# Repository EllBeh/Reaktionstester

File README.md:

# Reaktionstester
Aufbau und Entwurf eines einfachen Reaktionstesters auf dem ATMEGA328P in C. Das Repository enthält dabei den Code sowie den Schaltplan und das Platinen-Layout. Der Code wurde auf dem Arduino UNO ausgeführt werden, weshalb die Code-Struktur der Arduinostruktur entspricht.

## Programmablaufplan

___
## Schaltplan

___
## Platinenlayout

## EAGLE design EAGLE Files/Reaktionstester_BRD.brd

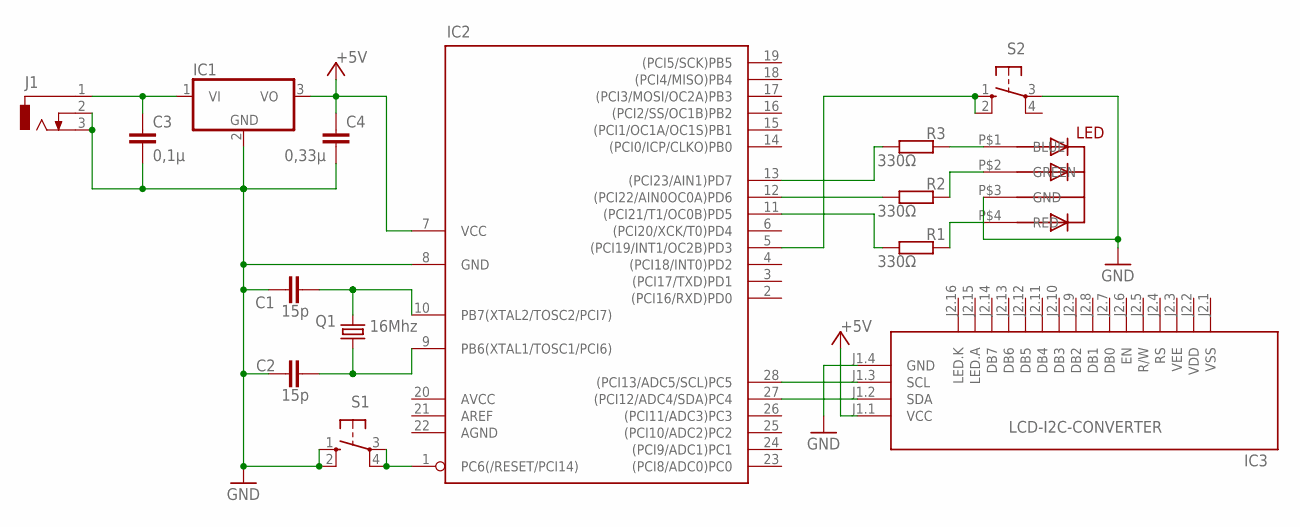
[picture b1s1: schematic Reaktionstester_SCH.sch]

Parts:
C1, C2: 15p; C5B3.5
C3: 0,1µ; C025-024X044
C4: 0,33µ; C025-024X044
IC1: 7805T; TO220H
IC2: ATMEGA328-20P; DIL28-3
IC3: LCD-I2C-CONVERTER
J1: DCJ0202
LED: 5MMRGBLED; LED5MMRGB
Q1: 16Mhz; 11.4X4.5
R1, R2, R3: 330Ω; 0204/5
S1, S2: 10-XX; B3F-10XX

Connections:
+5V: C4.1, IC1.3 (VO), IC2.7 (VCC), IC3.J1.1 (VCC)
GND: C1.1, C2.1, C3.2, C4.2, IC1.2 (GND), IC2.8 (GND), IC3.J1.4 (GND), J1.2, J1.3, LED.P$3 (GND), S1.1 (S), S1.2 (S1), S2.3, S2.4 (P1)
unnamed: C1.2, IC2.10 (PB7(XTAL2/TOSC2/PCI7)), Q1.2
unnamed: LED.P$1 (BLUE), R3.1
unnamed: C2.2, IC2.9 (PB6(XTAL1/TOSC1/PCI6)), Q1.1
unnamed: IC2.11 ((PCI21/T1/OC0B)PD5), R1.2
unnamed: IC2.5 ((PCI19/INT1/OC2B)PD3), S2.1 (S), S2.2 (S1)
unnamed: IC2.12 ((PCI22/AIN0OC0A)PD6), R2.2
unnamed: IC2.13 ((PCI23/AIN1)PD7), R3.2
unnamed: C3.1, IC1.1 (VI), J1.1
unnamed: LED.P$2 (GREEN), R2.1
unnamed: LED.P$4 (RED), R1.1
unnamed: IC2.28 ((PCI13/ADC5/SCL)PC5), IC3.J1.3 (SCL)
unnamed: IC2.1 (PC6(/RESET/PCI14)), S1.3, S1.4 (P1)
unnamed: IC2.27 ((PCI12/ADC4/SDA)PC4), IC3.J1.2 (SDA)

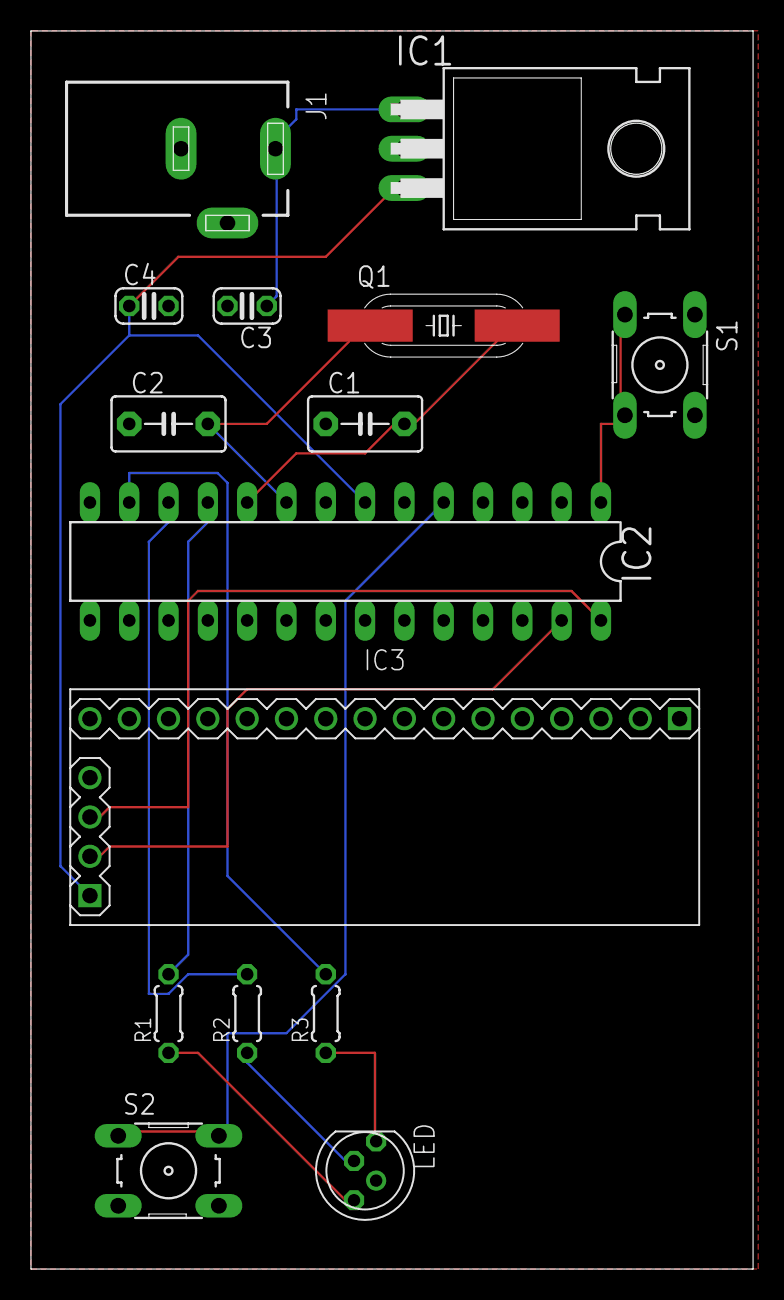
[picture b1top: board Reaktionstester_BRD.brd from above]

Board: 2 copper layers, 46.7 x 80.0 mm, 15 parts (0 on the bottom side), 15 nets.

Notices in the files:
parts and their libraries:
diy-modules: Released under the Creative Commons Attribution 4.0 International License: http://creativecommons.org/licenses/by/4.0
crystal-geyer_V1_0: Copyright: Geyer-Electronic
